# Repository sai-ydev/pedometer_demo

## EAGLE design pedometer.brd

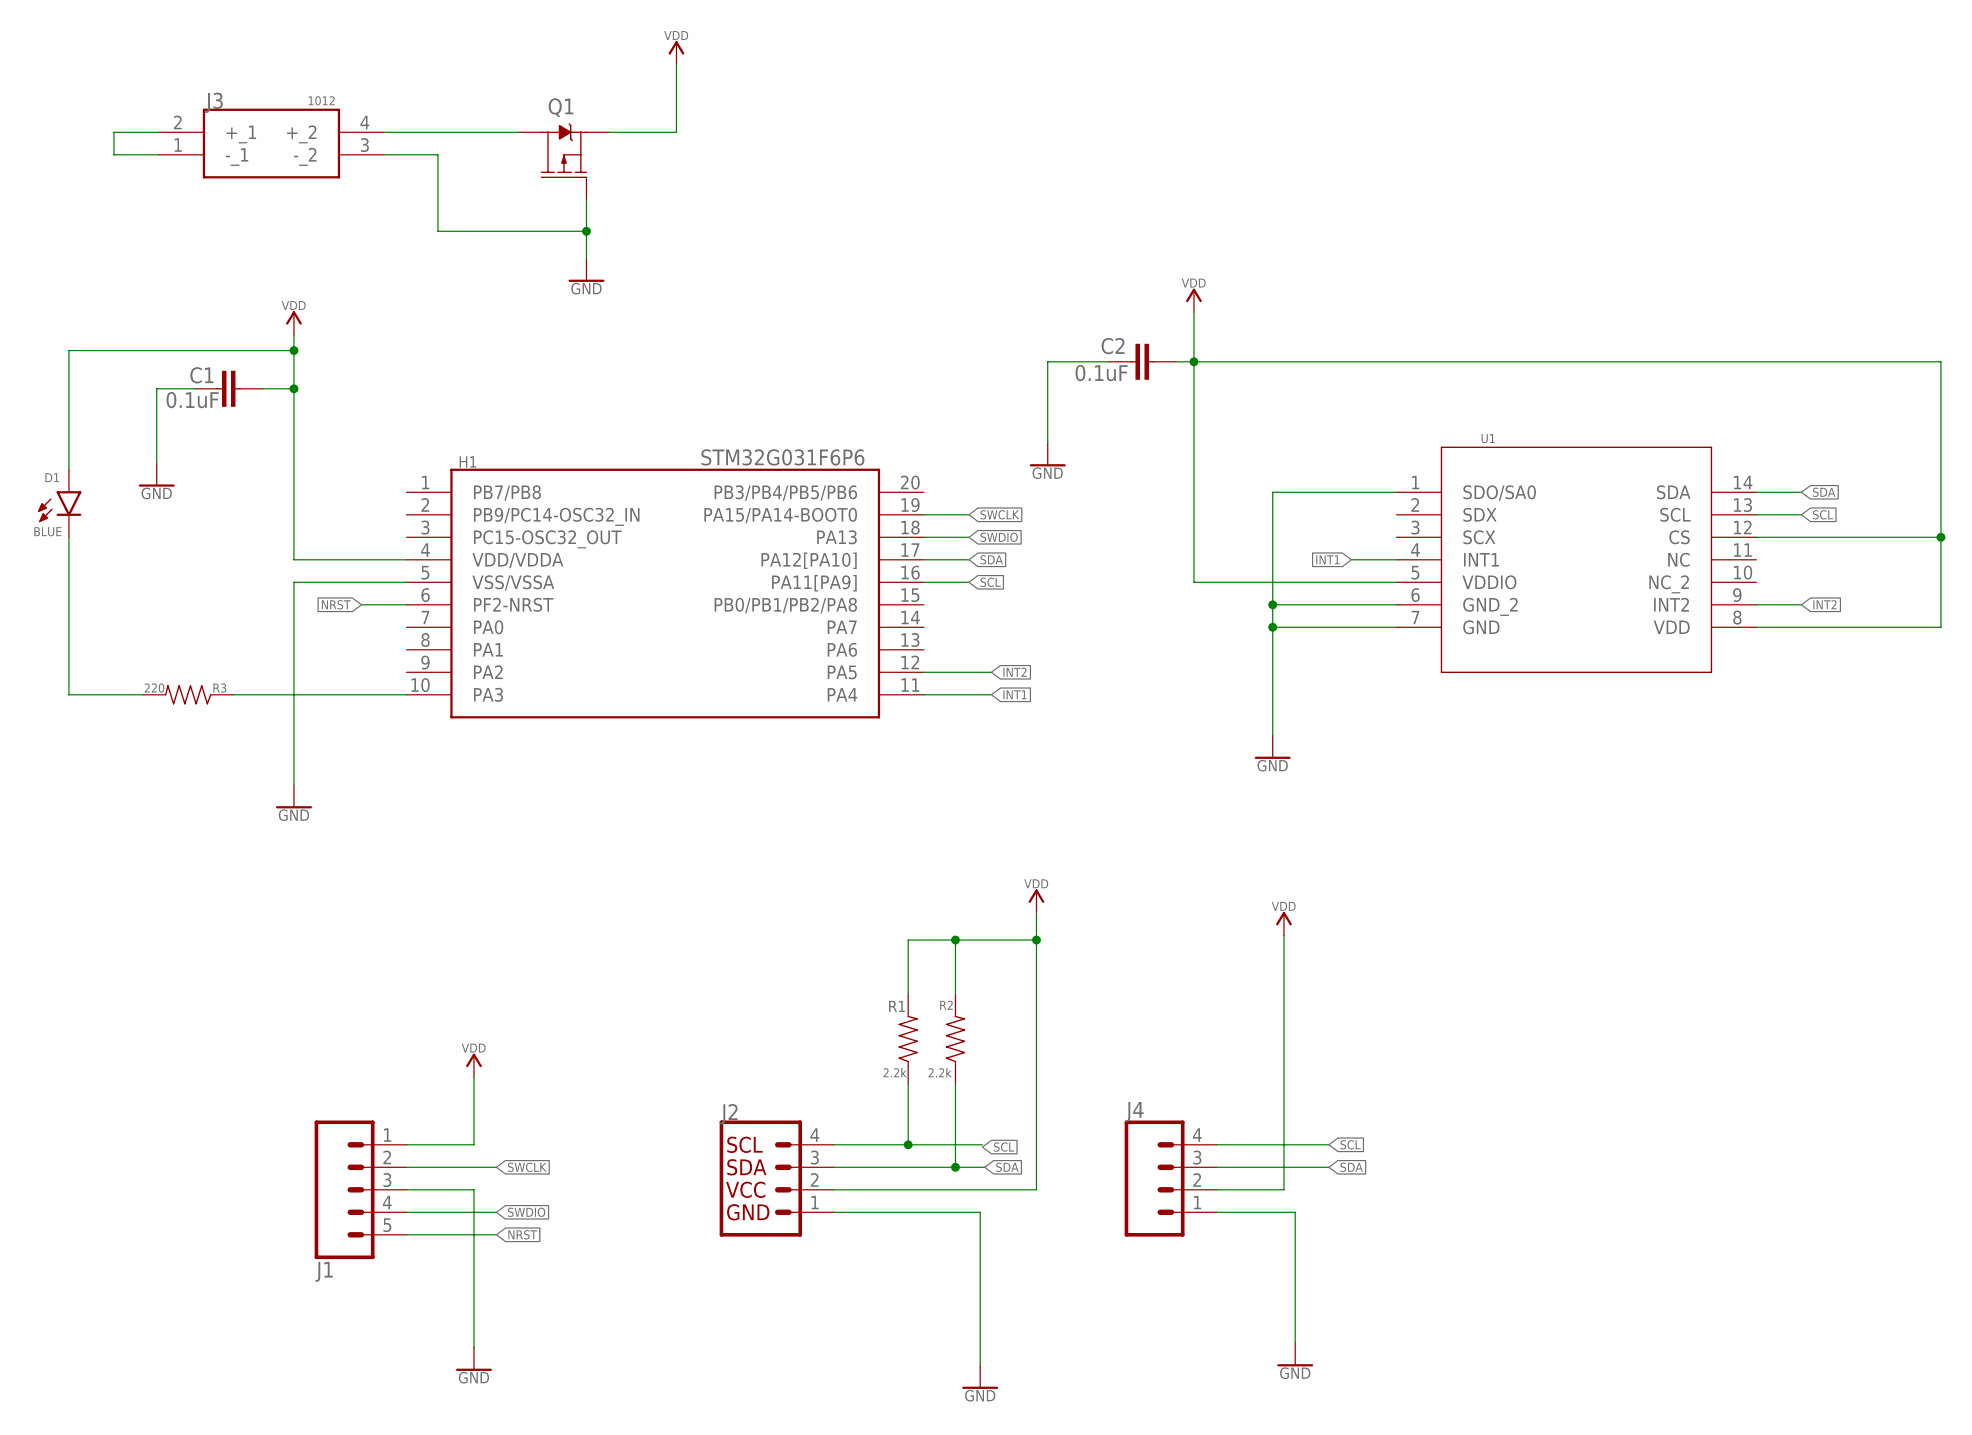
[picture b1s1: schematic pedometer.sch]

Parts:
C1, C2: 0.1uF; 0603
D1: BLUE; LED-0603
H1: STM32G031F6P6; SOP65P640X120-20N
J1: CONN_05; 1X05
J2: QWIIC_CONNECTORJS-1MM; 1X04_1MM_RA
J3: 1012
J4: CONN_04; 1X04
Q1: 2.5A/30V/105mΩ; SOT23-3
R1, R2: 2.2k; 0603
R3: 220; 0603
U1: LSM6DSO32TRLGA-14L_2P5X3X0P83_STM-M; LGA-14L_2P5X3X0P83_STM-M

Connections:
GND: C1.1, C2.1, H1.5 (VSS/VSSA), J1.3, J2.1, J3.3 (-_2), J4.1 (VCC), Q1.1 (G), U1.1 (SDO/SA0), U1.6 (GND_2), U1.7 (GND)
INT1: H1.11 (PA4), U1.4 (INT1)
INT2: H1.12 (PA5), U1.9 (INT2)
unnamed: J3.1 (-_1), J3.2 (+_1)
unnamed: J3.4 (+_2), Q1.3 (D)
unnamed: H1.10 (PA3), R3.1
unnamed: D1.C, R3.2
NRST: H1.6 (PF2-NRST), J1.5
SCL: H1.16 (PA11[PA9]), J2.4, J4.4 (GND), R1.1, U1.13 (SCL)
SDA: H1.17 (PA12[PA10]), J2.3, J4.3 (SDA), R2.1, U1.14 (SDA)
SWCLK: H1.19 (PA15/PA14-BOOT0), J1.2
SWDIO: H1.18 (PA13), J1.4
VDD: C1.2, C2.2, D1.A, H1.4 (VDD/VDDA), J1.1, J2.2, J4.2 (SCL), Q1.2 (S), R1.2, R2.2, U1.5 (VDDIO), U1.8 (VDD), U1.12 (CS)

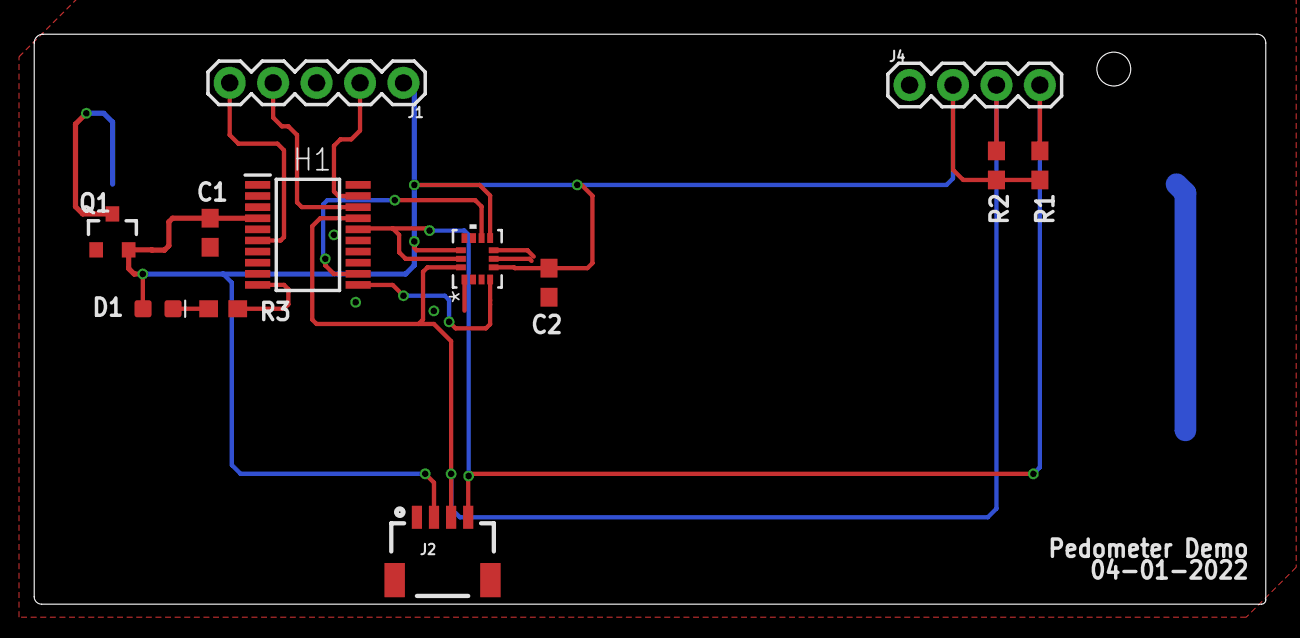
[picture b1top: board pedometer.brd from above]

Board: 2 copper layers, 72.0 x 33.3 mm, 13 parts (1 on the bottom side), 13 nets.

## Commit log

2022-04-01 Included requisite libraries.
2022-04-01 COmpleted board files

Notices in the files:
parts and their libraries:
SparkFun-Connectors: Licensing: Creative Commons ShareAlike 4.0 International - https://creativecommons.org/licenses/by-sa/4.0
COPYRIGHT: Copyright (C) 2022 Ultra Librarian. All rights reserved.
